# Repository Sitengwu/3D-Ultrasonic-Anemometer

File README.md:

# 3D Ultrasonic Anemometer
 Design documentation for a 3D ultrasonic anemometer

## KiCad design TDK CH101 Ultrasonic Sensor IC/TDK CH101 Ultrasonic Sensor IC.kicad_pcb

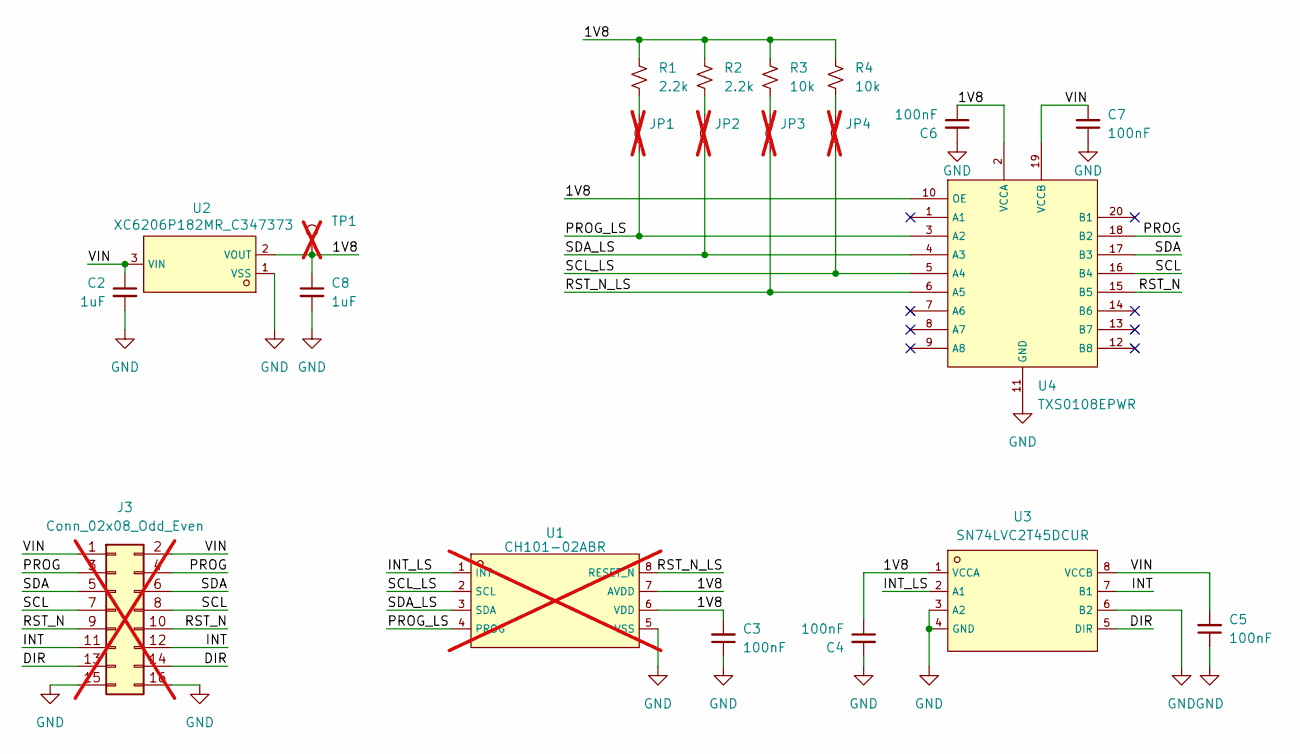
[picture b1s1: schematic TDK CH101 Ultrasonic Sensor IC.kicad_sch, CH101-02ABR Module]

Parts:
C2, C8: 1uF; C_0603_1608Metric; LCSC C15849
C3, C4, C5, C6, C7: 100nF; C_0603_1608Metric; LCSC C14663
J3: Conn_02x08_Odd_Even; PinHeader_2x08_P2.54mm_Vertical; not fitted
JP1, JP2, JP3, JP4: Jumper_2_Small_Bridged; SolderJumper-2_P1.3mm_Open_TrianglePad1.0x1.5mm; not fitted
R1, R2: 2.2k; R_0603_1608Metric; LCSC C4190
R3, R4: 10k; R_0603_1608Metric; LCSC C25804
TP1: TestPoint; TestPoint_Pad_1.0x1.0mm; not fitted
U1: CH101-02ABR; LGA-8_L3.5-W3.5-P0.50-TL; LCSC C1513113; not fitted
U2: XC6206P182MR_C347373; SOT-23-3_L3.0-W1.7-P0.95-LS2.9-BR; LCSC C347373
U3: SN74LVC2T45DCUR; VSSOP-8_L2.4-W2.1-P0.50-LS3.2-BR; LCSC C15741
U4: TXS0108EPWR; TSSOP-20_L6.5-W4.4-P0.65-LS6.4-BL; LCSC C17206

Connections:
/1V8: C3.2, C4.1, C6.1, C8.1, R1.1, R2.1, R3.1, R4.1, TP1.1, U1.6 (VDD), U1.7 (AVDD), U2.2 (VOUT), U3.1 (VCCA), U4.2 (VCCA), U4.10 (OE)
/DIR: J3.13, J3.14, U3.5 (DIR)
/INT: J3.11, J3.12, U3.7 (B1)
/INT_LS: U1.1 (INT), U3.2 (A1)
/PROG: J3.3, J3.4, U4.18 (B2)
/PROG_LS: JP1.1 (A), U1.4 (PROG), U4.3 (A2)
/RST_N: J3.9, J3.10, U4.15 (B5)
/RST_N_LS: JP3.1 (A), U1.8 (RESET_N), U4.6 (A5)
/SCL: J3.7, J3.8, U4.16 (B4)
/SCL_LS: JP4.1 (A), U1.2 (SCL), U4.5 (A4)
/SDA: J3.5, J3.6, U4.17 (B3)
/SDA_LS: JP2.1 (A), U1.3 (SDA), U4.4 (A3)
/VIN: C2.1, C5.2, C7.2, J3.1, J3.2, U2.3 (VIN), U3.8 (VCCB), U4.19 (VCCB)
GND: C2.2, C3.1, C4.2, C5.1, C6.2, C7.1, C8.2, J3.15, J3.16, U1.5 (VSS), U2.1 (VSS), U3.3 (A2), U3.4 (GND), U3.6 (B2), U4.11 (GND)
unnamed: JP1.2 (B), R1.2
unnamed: JP2.2 (B), R2.2
unnamed: JP3.2 (B), R3.2
unnamed: JP4.2 (B), R4.2

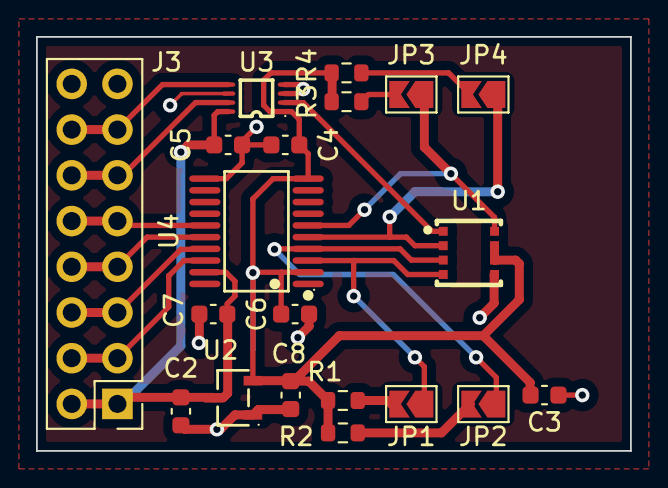
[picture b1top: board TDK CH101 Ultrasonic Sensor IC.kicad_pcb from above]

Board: 2 copper layers, 33.0 x 23.0 mm, 21 parts (1 on the bottom side), 18 nets.

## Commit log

2025-04-11 ADD: TDK Sensor
2025-04-19 Update: TDK CH101 complete PCB
2025-04-23 Update: CH101 production settings
2025-07-03 Complete S1V1 and Solution S2V2
